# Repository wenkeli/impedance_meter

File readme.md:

Electronics to measure the resistance of multi-channel animal electrodes

This project uses the Analog Devices AD5934 impedance measurement chip with the STM32 micro-controller to measure 32 channel tetrode channel assemblies, and the ability to pass up to 5uA of current through a 2 MOhm electrode, useful for lesioning the tissue surrounding the electrodes.

The firmware folder contains the STM32 MCU code for controlling the AD5934 chip and defines the user interface on the touch screen.

The hardware folder contains the schematics and PCB designs of the electronics.

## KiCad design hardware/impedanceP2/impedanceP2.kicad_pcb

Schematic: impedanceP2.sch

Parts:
C1, C2, C4, C5, C10, C13: 4.7uF; SM0603; digikey 587-2786-1-ND
C3, C11: 10uF; SM0603; digikey 587-3238-1-ND
C6, C8, C9: 100uF; SM1210; digikey 587-3152-1-ND
C7: 300pF; SM0603; digikey 1276-2261-1-ND
D1: LED; 0603; digikey 160-1447-1-ND
D3: B220A; SMA; digikey B220A-FDICT-ND
FI1: ELK-E333FA; digikey P13159CT-ND
J1, J2: RJ45; RJ45-8; digikey 609-1046-ND
J3: USB; digikey 670-1190-1-ND
L1: 4.7uH; digikey 308-2050-1-ND
L3, L4: 33uH; digikey 445-1983-1-ND
MCP1: MCP73831; SOT23-5; digikey MCP73831T-2ATI/OTCT-ND
P1: JST-PH2; jst-ph-JST-PH2; digikey 455-1719-ND
P2, P3: CONN_24X2
Q1, Q2: DMG2307L-7; SOT-23; digikey DMG2307L-7DICT-ND
R1: 300; SM0603; digikey 1276-4599-1-ND
R2: 2K; SM0603; digikey 311-2.00KHRCT-ND
R3, R35: 100K; SM0603; digikey 311-100KHRCT-ND
R4, R5, R10, R11, R20, R21, R22, R23, R24, R25, R34: 47K; SM0603; digikey 311-47.0KHRCT-ND
R6: 0.42; SM0805; digikey P.43BHCT-ND
R7: 180; SM0805; digikey P180ADCT-ND
R8: 10K; SM0603; digikey 311-10.0KHRCT-ND
R9: 71.5K; SM0603; digikey 311-71.5KHRCT-ND
R12, R13, R14, R15, R16, R17, R18, R19, R26, R27, R30: 95.3K; SM0603; digikey P95.3KHCT-ND
R28, R29, R32, R33: 4.7K; SM0603; digikey 311-4.70KHRCT-ND
R31: 200K; SM0603; digikey 311-200KHRCT-ND
SW1: SWITCH_INV; digikey EG2585-ND
U1: MC34063; SOIC8; digikey 296-17765-1-ND
U2: ISL9111; SOT23_6; digikey 296-17765-1-ND
U3, U4, U5: LM324QUAD; TSSOP14; digikey 296-9544-1-ND
U6: PCA9306; SM8; digikey 296-18509-1-ND

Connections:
+5V: C1.1, J3.1, MCP1.4, R1.2
/3.3VOUT: P2.48, R28.1, R29.2, U6.2
/5VOUT: J1.7, P2.2, P3.2, Q2.S, R31.1, R32.1, R33.2
/10VOUT: C4.1, C9.1, C10.1, C13.2, J1.2, L4.2, U3.4, U4.4, U5.4
/INH: P2.9, U5.10
/INHV10: J1.3, R30.1, U5.8
/SCL: P2.44, R28.2, U6.3
/SCL5V: J2.1, R32.2, U6.6
/SDA: P2.45, R29.1, U6.4
/SDA5V: J2.2, R33.1, U6.5
/VBAT: C11.1, MCP1.3, P1.1, SW1.2
/VMOS: C3.2, C6.1, L1.2, Q1.S, R6.1, U1.6, U2.3, U2.6
/X2: P2.3, U4.3
/X2V10: J2.4, R14.2, U4.1
/X4A: P2.7, U5.3
/X4AV10: J2.8, R26.2, U5.1
/X4B: P2.8, U5.5
/X4BV10: J2.7, R27.2, U5.7
/X8A: P2.4, U4.5
/X8AV10: J2.3, R15.2, U4.7
/X8B: P2.5, U4.10
/X8BV10: J2.6, R19.1, U4.8
/X8C: P2.6, U4.12
/X8CV10: J2.5, R18.1, U4.14
/X16S0: P3.3, U3.3
/X16S0V10: J1.5, R12.2, U3.1
/X16S1: P3.4, U3.5
/X16S1V10: J1.4, R13.2, U3.7
/X16S2: P3.5, U3.10
/X16S2V10: J1.8, R17.1, U3.8
/X16S3: P3.6, U3.12
/X16S3V10: J1.6, R16.1, U3.14
GND: C1.2, C2.1, C3.1, C4.2, C5.2, C6.2, C7.1, C8.2, C9.2, C10.2, C11.2, C13.1, FI1.2, J1.1, J3.5, MCP1.2, P1.2, P2.47, P3.1, R2.2, R3.1, R4.1, R5.1, R8.2, R10.1, R11.1, R20.2, R21.2, R22.2, R23.2, R24.1, R25.1, R34.2, R35.1, U1.2, U1.4, U2.2, U3.11, U4.11, U5.11, U6.1
unnamed: C2.2, R31.2, U6.7, U6.8
unnamed: R5.2, R13.1, U3.6
unnamed: R4.2, R12.1, U3.2
unnamed: R16.2, R20.1, U3.13
unnamed: R17.2, R21.1, U3.9
unnamed: R8.1, R9.2, U1.5
unnamed: D3.1, L3.2, U1.1
unnamed: L3.1, R6.2, R7.1, U1.7
unnamed: R7.2, U1.8
unnamed: C7.2, U1.3
unnamed: C5.1, FI1.1, U2.5
unnamed: L1.1, U2.1
unnamed: FI1.3, Q2.D
unnamed: C8.1, D3.2, L4.1, R9.1
unnamed: R25.2, R27.1, U5.6
unnamed: R24.2, R26.1, U5.2
unnamed: R30.2, R34.1, U5.9
unnamed: Q2.G, R35.2
unnamed: R18.2, R22.1, U4.13
unnamed: R10.2, R14.1, U4.2
unnamed: R11.2, R15.1, U4.6
unnamed: R19.2, R23.1, U4.9
unnamed: D1.2 (K), MCP1.1
unnamed: MCP1.5, R2.1
unnamed: D1.1 (A), R1.1
unnamed: Q1.D, SW1.3
unnamed: Q1.G, R3.2

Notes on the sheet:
PE0
PE1
PE2
PE4
PE6
PE3
PE5
PB12
PB14
PB13
PB15
PB10
PB11

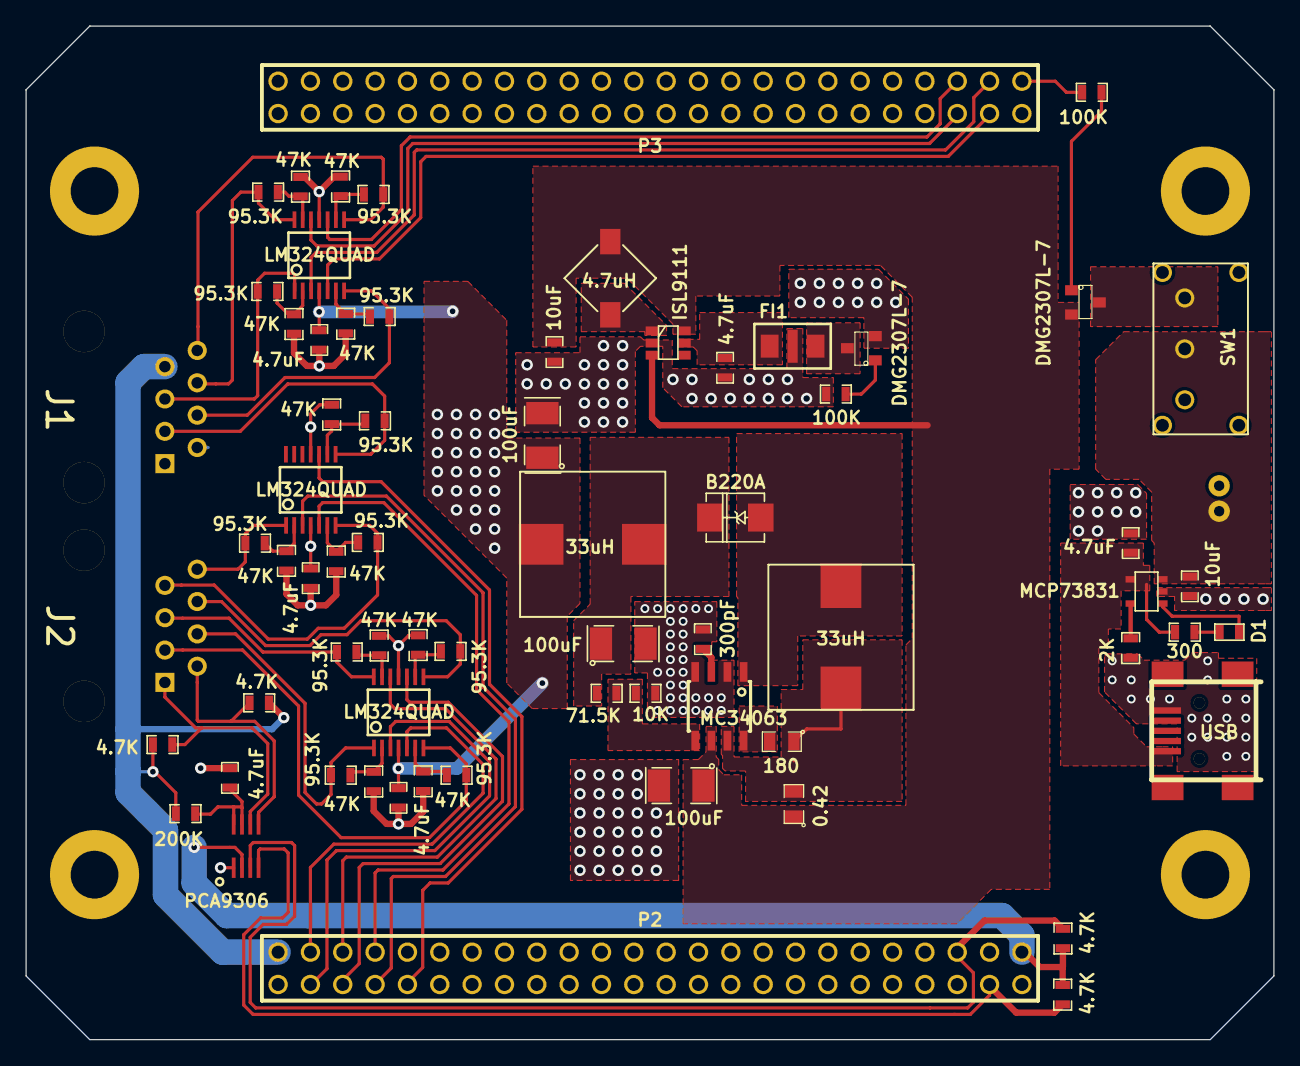
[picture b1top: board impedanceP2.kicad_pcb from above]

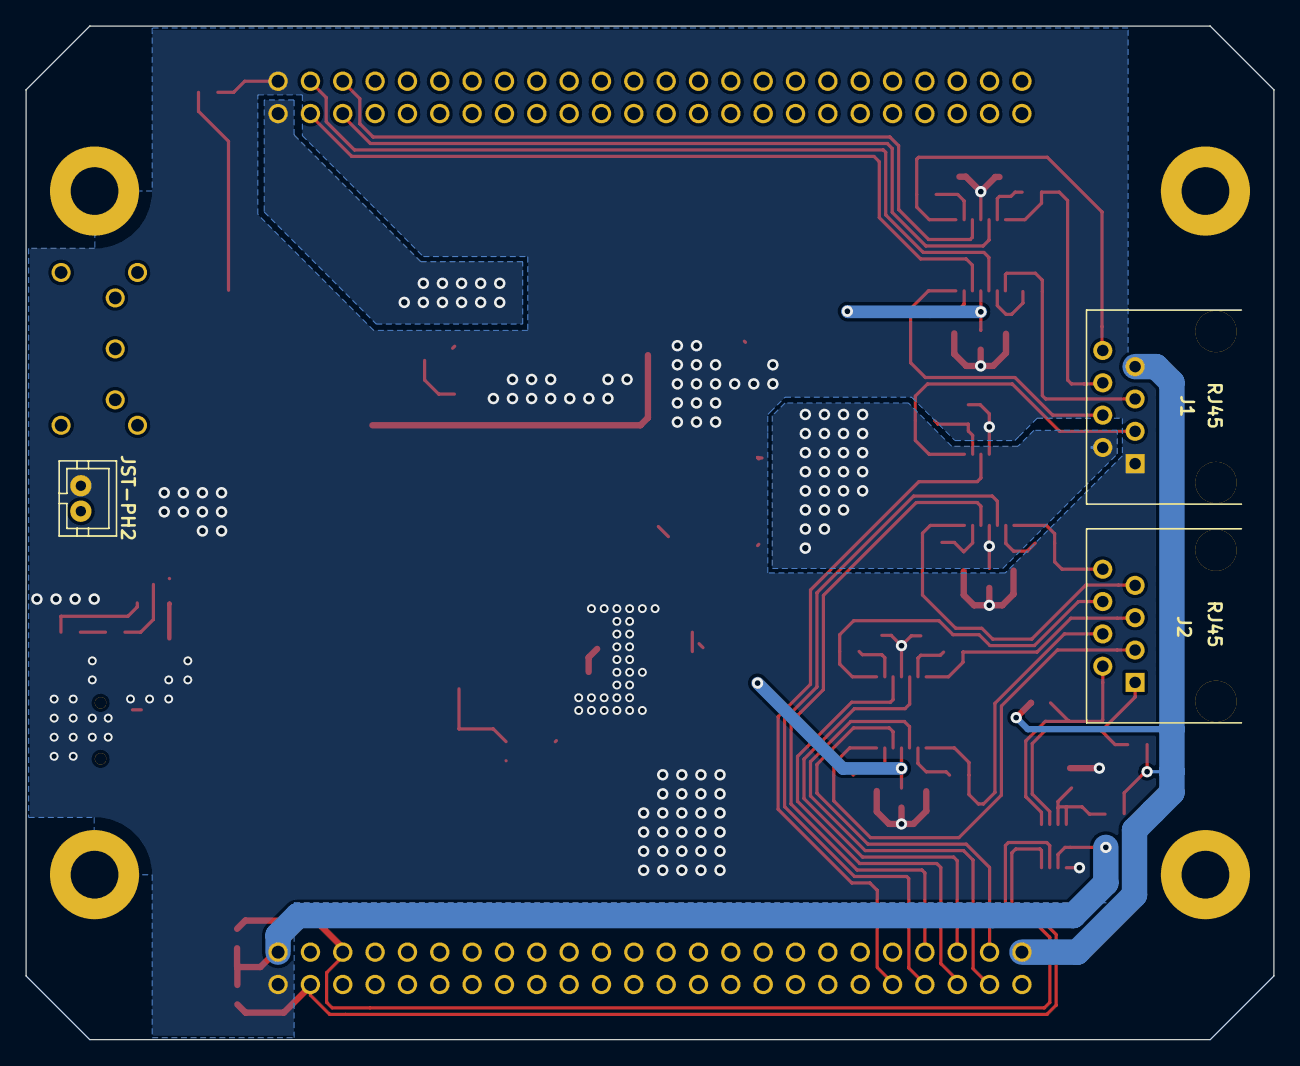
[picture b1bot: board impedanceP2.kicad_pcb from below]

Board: 2 copper layers, 98.0 x 79.6 mm, 73 parts (3 on the bottom side), 60 nets.

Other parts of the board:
PIN_ARRAY_1, PIN_ARRAY_1#2, PIN_ARRAY_1#3, PIN_ARRAY_1#4: Val**; PIN_ARRAY_1

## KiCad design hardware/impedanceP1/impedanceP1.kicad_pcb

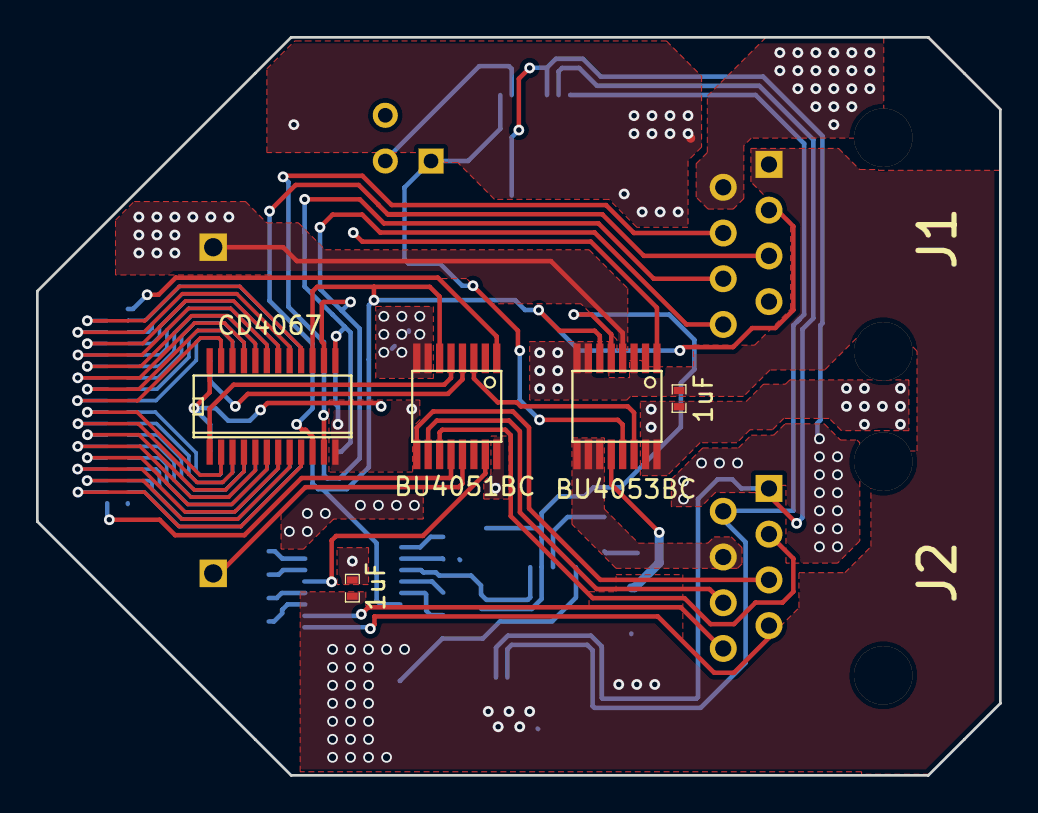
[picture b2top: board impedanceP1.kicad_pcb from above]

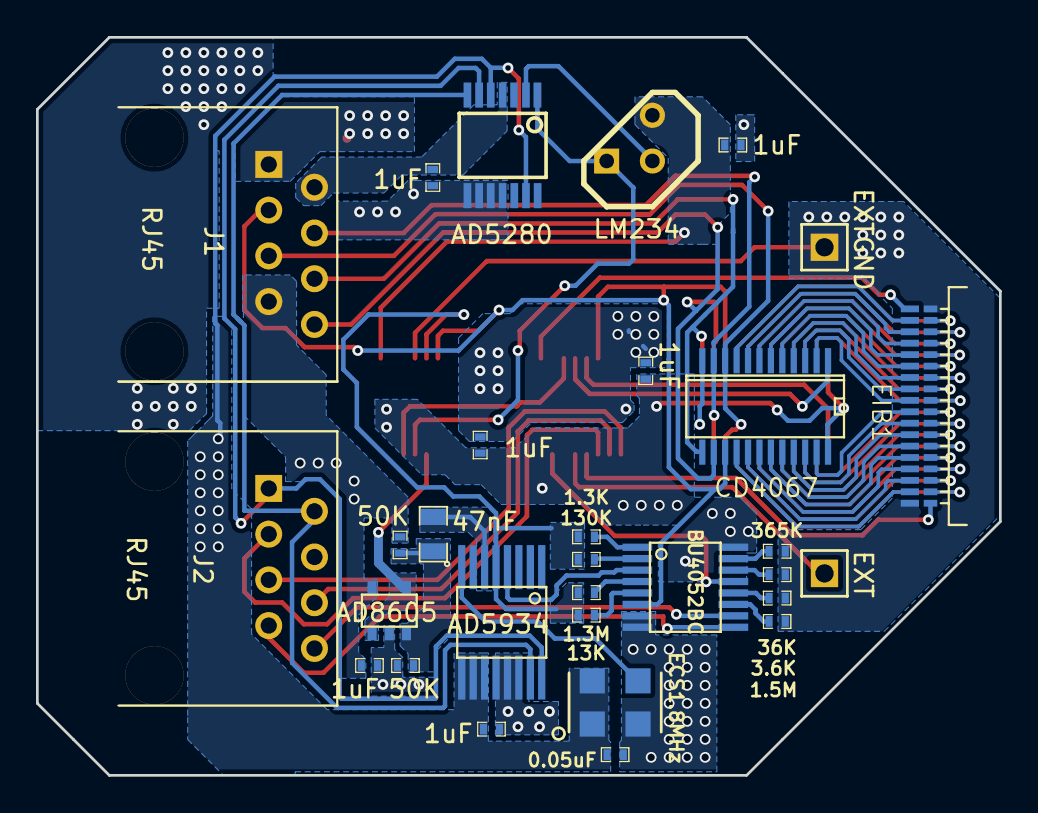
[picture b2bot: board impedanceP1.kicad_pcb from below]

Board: 2 copper layers, 53.5 x 41.0 mm, 35 parts (30 on the bottom side), 73 nets.

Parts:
AD1: AD5934; ssop-16
AD2: AD8605; SOT23-5
BU0: BU4053BC; ssop-16
BU1: BU4051BC; ssop-16
BU2: BU4052BC; ssop-16
C1, C2, C3, C4, C5, C6, C7, C10: 1uF; SM0402_c
C8: 0.05uF; SM0402_c
C9: 47nF; SM0805
EIB1: OMNETICS_EIB36; OMNETICS_A79025
EXT1: EXT; PIN_ARRAY_1
EXTGND1: EXTGND; PIN_ARRAY_1
J1, J2: RJ45; RJ45_8
OSC1: ECS3961_3; ECS3963_1
R1: 1.3K; SM0402_r
R2: 130K; SM0402_r
R3: 1.3M; SM0402_r
R4: 13K; SM0402_r
R5: 3.6K; SM0402_r
R6: 365K; SM0402_r
R7: 1.5M; SM0402_r
R8: 36K; SM0402_r
R9, R10: 50K; SM0402_r
U1, U2: CD4067; SSOP24
U3: AD5280; SSOP14
U4: LM234; TO92

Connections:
/5VOUT: AD1.9, AD1.10, AD1.11, AD2.5, C2.2, C8.2, C10.2, J1.7, OSC1.1, OSC1.4, R10.2, U3.5, U3.13
/10VOUT: BU0.15, BU0.16, BU1.16, BU2.16, C1.2, C3.2, C4.2, C5.2, C6.2, J1.2, U1.24, U2.24, U3.4
/B2: EIB1.20, U1.9
/B3: EIB1.21, U1.8
/B4: EIB1.22, U1.7
/B5: EIB1.23, U1.6
/B6: EIB1.24, U1.5
/B7: EIB1.25, U1.4
/B8: EIB1.26, U1.3
/B9: EIB1.27, U1.2
/B10: EIB1.28, U1.23
/B11: EIB1.29, U1.22
/B12: EIB1.30, U1.21
/B13: EIB1.31, U1.20
/B14: EIB1.32, U1.19
/B15: EIB1.33, U1.18
/B16: EIB1.34, U1.17
/B17: EIB1.35, U1.16
/CAL: BU1.15, BU2.13
/CURPROG: U3.2, U4.2
/CURPWR: BU0.1, C7.2, U4.3
/CURSRC: BU0.13, U3.1, U4.1
/EIBGND: BU0.4, EIB1.18, EIB1.36, EXTGND1.1, R5.2, R6.2, R7.2, R8.2
/EXT: BU1.13, EXT1.1
/INHV10: BU0.6, BU1.6, BU2.6, J1.3, U1.15, U2.15
/PWOUT: BU0.14, BU1.3
/REF1: BU1.1, EIB1.1
/REF2: BU1.12, EIB1.19
/RFB: AD1.4, BU2.3
/SCL5V: AD1.16, J2.1, U3.6
/SDA5V: AD1.15, J2.2, U3.7
/T2: EIB1.2, U2.9
/T3: EIB1.3, U2.8
/T4: EIB1.4, U2.7
/T5: EIB1.5, U2.6
/T6: EIB1.6, U2.5
/T7: EIB1.7, U2.4
/T8: EIB1.8, U2.3
/T9: EIB1.9, U2.2
/T10: EIB1.10, U2.23
/T11: EIB1.11, U2.22
/T12: EIB1.12, U2.21
/T13: EIB1.13, U2.20
/T14: EIB1.14, U2.19
/T15: EIB1.15, U2.18
/T16: EIB1.16, U2.17
/T17: EIB1.17, U2.16
/TESTIN: AD1.5, BU0.5, R1.1, R2.1, R3.1, R4.1
/TESTOUT: AD2.1, AD2.4, BU0.12
/TOUTAMP: AD2.3, C9.1, R9.2, R10.1
/X2V10: BU0.9, BU0.10, BU0.11, J2.4
/X4AV10: BU2.10, J2.8
/X4BV10: BU2.9, J2.7
/X8AV10: BU1.11, J2.3
/X8BV10: BU1.10, J2.6
/X8CV10: BU1.9, J2.5
/X16A: BU1.5, U1.1
/X16B: BU1.4, U2.1
/X16S0V10: J1.5, U1.10, U2.10
/X16S1V10: J1.4, U1.11, U2.11
/X16S2V10: J1.8, U1.14, U2.14
/X16S3V10: J1.6, U1.13, U2.13
GND: AD1.12, AD1.13, AD1.14, AD2.2, BU0.3, BU0.7, BU0.8, BU1.7, BU1.8, BU2.7, BU2.8, C1.1, C2.1, C3.1, C4.1, C5.1, C6.1, C7.1, C8.1, C10.1, J1.1, OSC1.2, R9.1, U1.12, U2.12, U3.8, U3.9, U3.10, U3.11
unnamed: BU2.11, R7.1
unnamed: BU2.14, R8.1
unnamed: BU2.5, R4.2
unnamed: BU2.15, R6.1
unnamed: BU2.12, R5.1
unnamed: AD1.8, OSC1.3
unnamed: AD1.6, C9.2
unnamed: BU2.2, R2.2
unnamed: BU2.1, R1.2
unnamed: BU2.4, R3.2

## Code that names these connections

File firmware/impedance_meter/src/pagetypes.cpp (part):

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				INTLABEL, 5, "", 0, 1000);
		curY=curY+40;
	}
	miscCHLabels[0].setStr("EXT CH");
	miscCHLabels[1].setStr("REF1 CH");
	miscCHLabels[2].setStr("REF2 CH");

	curY=25;
	buttonSY=30;
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	startY=startY+45;

	extCHLabel.setParams(startX, startY, VGA_WHITE, bgColor,
			SmallFont, STRLABEL, 3, "EXT", 0, 1000);
	displayList[counter]=&extCHLabel;
	counter++;
	toggleExtCH.init(extCH);
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	startY=startY+30;

	ref1CHLabel.setParams(startX, startY, VGA_WHITE, bgColor,
				SmallFont, STRLABEL, 4, "REF1", 0, 1000);
	displayList[counter]=&ref1CHLabel;
	counter++;
	toggleRef1CH.init(ref1CH);
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	startY=startY+30;

	ref2CHLabel.setParams(startX, startY, VGA_WHITE, bgColor,
				SmallFont, STRLABEL, 4, "REF2", 0, 1000);
	displayList[counter]=&ref2CHLabel;
	counter++;
	toggleRef2CH.init(ref2CH);
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
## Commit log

2015-12-25 initial commit for hardware schematics
2015-12-26 added an empty main.cpp and made sure it’s not in the gitignore entry. this is needed for compilation to be successful in impedance_meter.
2019-11-28 updated to kicad 5 and clean up
2019-11-30 updated to kicad 5 and cleanup
2020-01-29 added initial readme
